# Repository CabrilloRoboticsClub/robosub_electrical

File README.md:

### Electrical stack up for RoboSub 2025 Lasershark

For documention take a look at:
https://github.com/CabrilloRoboticsClub/robosub_electrical/wiki

Desing requirments document:
https://docs.google.com/document/d/1Yq5ZJsRXAqFWiCNv81dD8MaTSv5xLRyw4zoX7664jJk/edit?usp=sharing

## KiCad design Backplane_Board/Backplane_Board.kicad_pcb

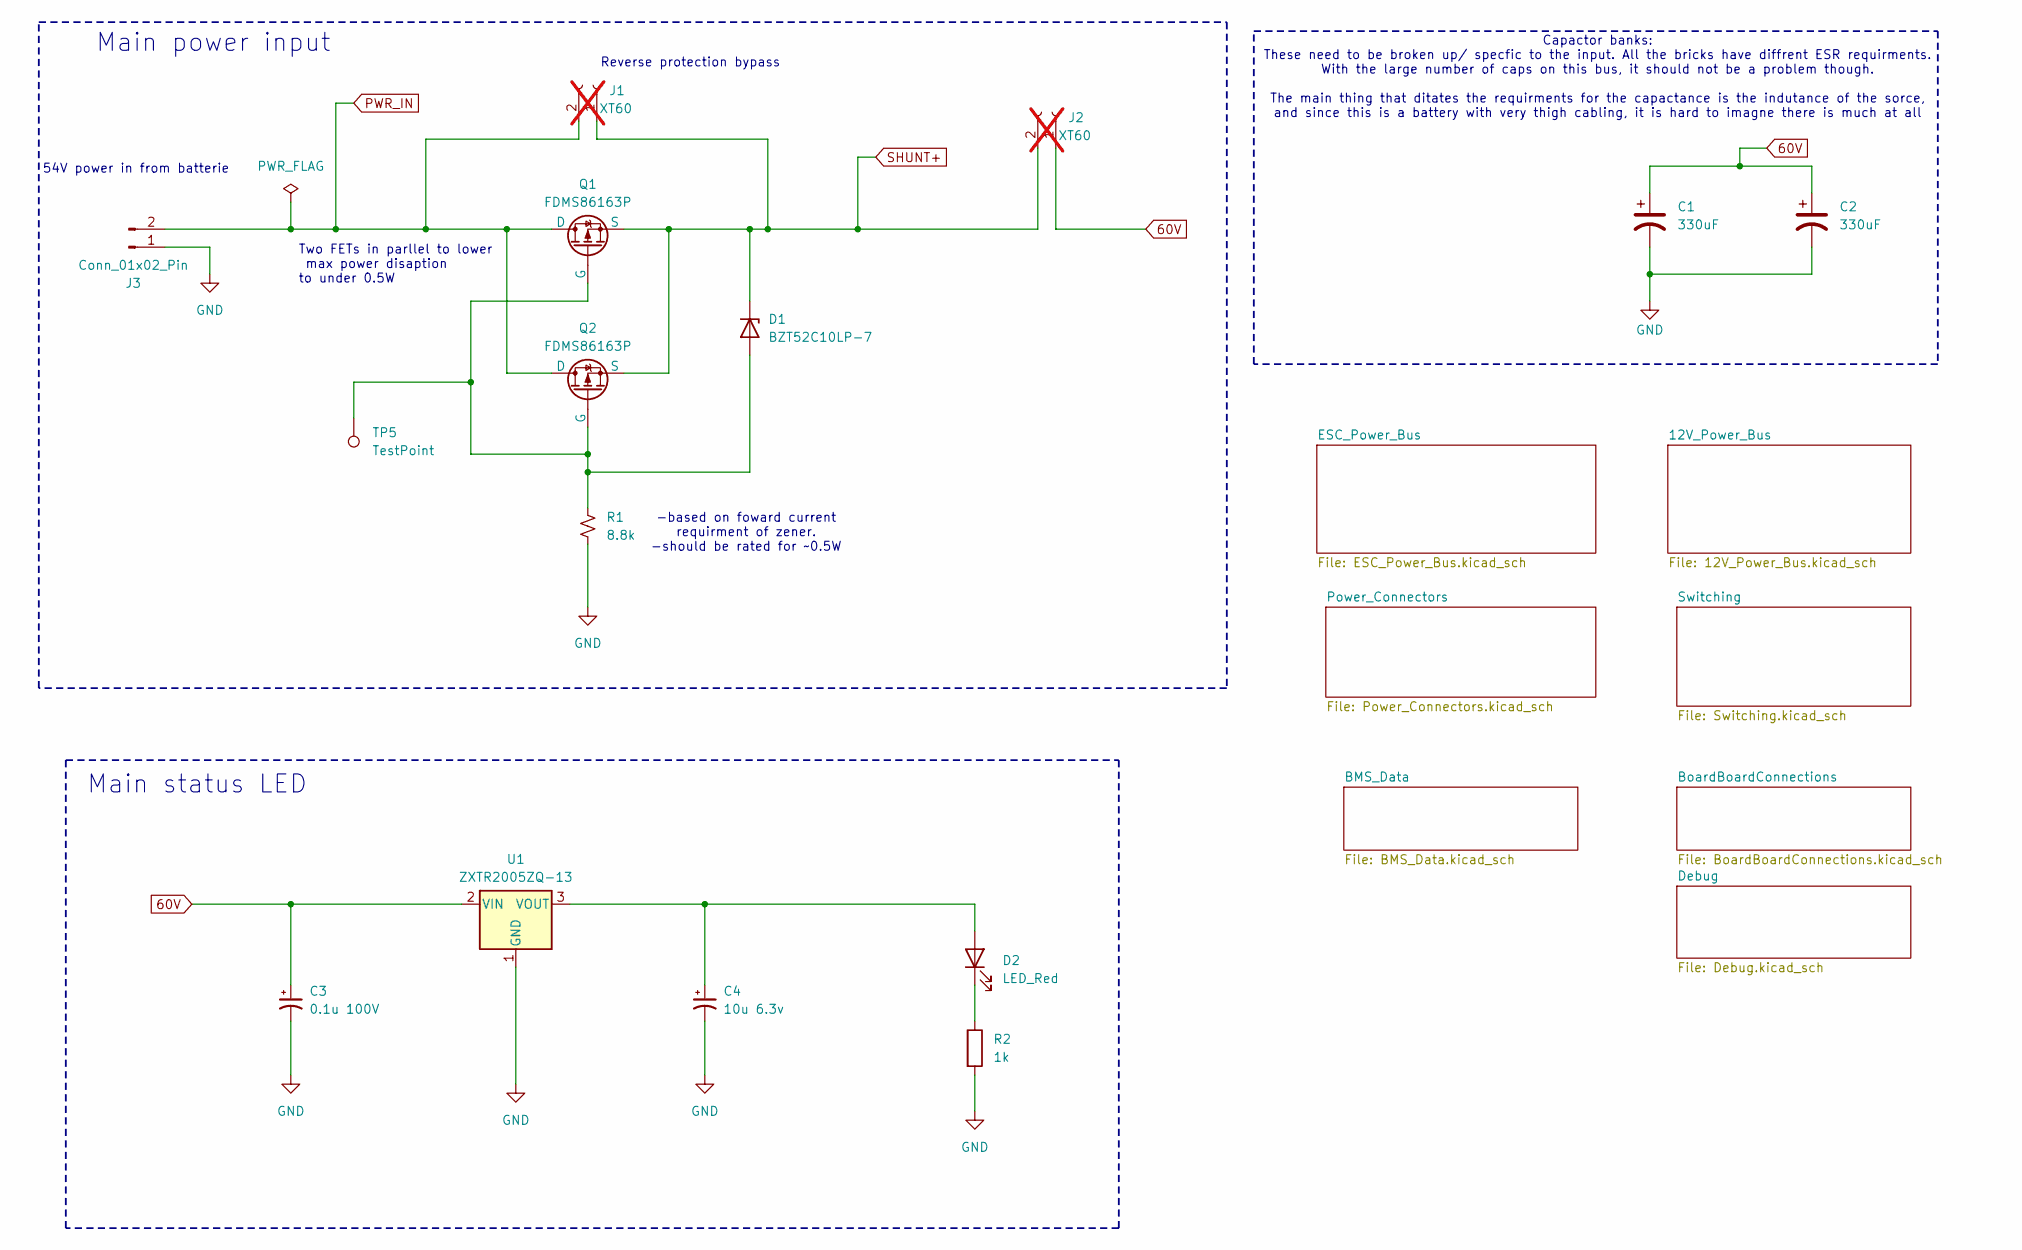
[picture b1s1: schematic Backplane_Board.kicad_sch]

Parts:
C1, C2: 330uF; CAP_EEVTG2A331M
C3: 0.1u 100V; C_1206_3216Metric_Pad1.33x1.80mm_HandSolder
C4: 10u 6.3v; C_1206_3216Metric_Pad1.33x1.80mm_HandSolder
D1: BZT52C10LP-7; D_SOD-882
D2: LED_Red; LED_0603_1608Metric
J1, J2: XT60; SolderWire-0.127sqmm_1x02_P3.7mm_D0.48mm_OD1mm; not fitted
J3: Conn_01x02_Pin; AMASS_XT60-M_1x02_P7.20mm_Vertical
Q1, Q2: FDMS86163P
R1: 8.8k; R_1206_3216Metric_Pad1.30x1.75mm_HandSolder
R2: 1k; R_0805_2012Metric_Pad1.20x1.40mm_HandSolder
TP5: TestPoint; TestPoint_Pad_2.5x2.5mm
U1: ZXTR2005ZQ-13; SOT-89-3_Handsoldering

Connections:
60V: C1.1, C2.1, C3.1, J2.1, U1.2 (VIN); also elsewhere on the board
GND: C1.2, C2.2, C3.2, C4.2, J3.1, R1.2, R2.2, U1.1 (GND); also elsewhere on the board
unnamed: D1.2 (A), Q1.2 (G), Q2.2 (G), R1.1, TP5.1
unnamed: C4.1, D2.2 (A), U1.3 (VOUT)
unnamed: D2.1 (K), R2.1
PWR_IN: J1.2, J3.2, Q1.1 (D), Q2.1 (D)
SHUNT+: D1.1 (K), J1.1, J2.2, Q1.3 (S), Q2.3 (S); also elsewhere on the board

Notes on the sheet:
Capactor banks: These need to be broken up/ specfic to the input. All the bricks have diffrent ESR requirments. With the large number of caps on this bus, it should not be a problem though. The main thing that ditates the requirments for the capactance is the indutance of the sorce, and since this 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
Main status LED
54V power in from batterie
Main power input
Reverse protection bypass
Two FETs in parllel to lower max power disaption to under 0.5W
-based on foward current requirment of zener. -should be rated for ~0.5W

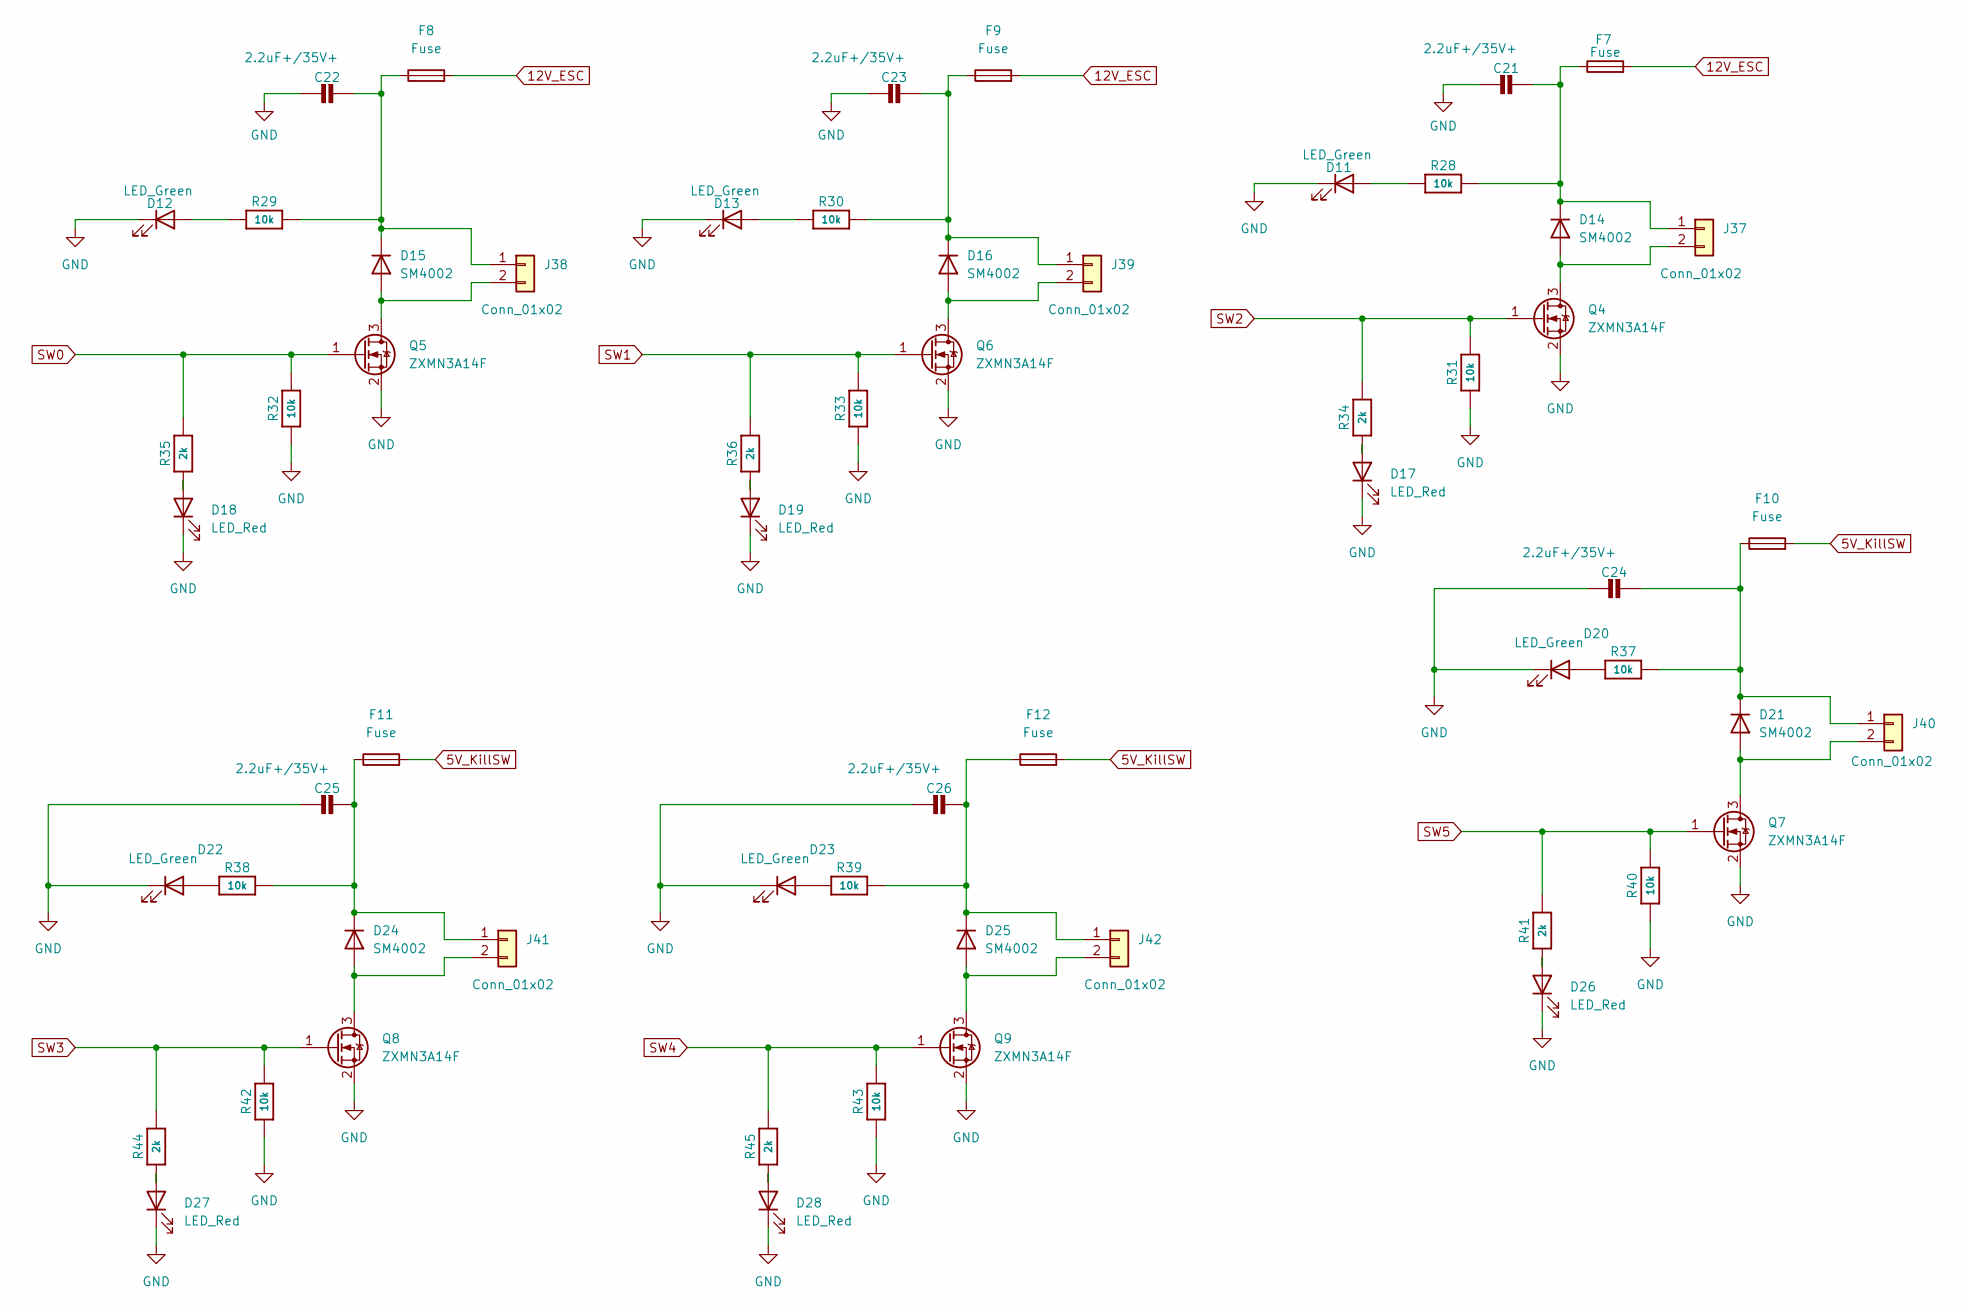
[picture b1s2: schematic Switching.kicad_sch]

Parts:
C21, C22, C23, C24, C25, C26: 2.2uF+/35V+; C_0805_2012Metric
D11, D12, D13, D20, D22, D23: LED_Green; LED_0603_1608Metric
D14, D15, D16, D21, D24, D25: SM4002; D_SOD-123F
D17, D18, D19, D26, D27, D28: LED_Red; LED_0603_1608Metric
F7, F8, F9, F10, F11, F12: Fuse; Fuse_0805_2012Metric
J37, J38, J39, J40, J41, J42: Conn_01x02; Molex_Micro-Latch_53253-0270_1x02_P2.00mm_Vertical
Q4, Q5, Q6, Q7, Q8, Q9: ZXMN3A14F; SOT-23
R28, R29, R30, R31, R32, R33, R37, R38, R39, R40, R42, R43: 10k; R_0805_2012Metric
R34, R35, R36, R41, R44, R45: 2k; R_0805_2012Metric

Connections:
5V_KillSW: F10.2, F11.2, F12.2; also elsewhere on the board
12V_ESC: F7.2, F8.2, F9.2; also elsewhere on the board
GND: C21.2, C22.2, C23.2, C24.2, C25.2, C26.2, D11.1 (K), D12.1 (K), D13.1 (K), D17.1 (K), D18.1 (K), D19.1 (K), D20.1 (K), D22.1 (K), D23.1 (K), D26.1 (K), D27.1 (K), D28.1 (K), Q4.2 (S), Q5.2 (S), Q6.2 (S), Q7.2 (S), Q8.2 (S), Q9.2 (S), R31.1, R32.1, R33.1, R40.1, R42.1, R43.1; also elsewhere on the board
unnamed: D11.2 (A), R28.1
unnamed: D12.2 (A), R29.1
unnamed: D13.2 (A), R30.1
unnamed: D14.2 (A), J37.2, Q4.3 (D)
unnamed: C21.1, D14.1 (K), F7.1, J37.1, R28.2
unnamed: D15.2 (A), J38.2, Q5.3 (D)
unnamed: C22.1, D15.1 (K), F8.1, J38.1, R29.2
unnamed: D16.2 (A), J39.2, Q6.3 (D)
unnamed: C23.1, D16.1 (K), F9.1, J39.1, R30.2
unnamed: D17.2 (A), R34.1
unnamed: D18.2 (A), R35.1
unnamed: D19.2 (A), R36.1
unnamed: D20.2 (A), R37.1
unnamed: D21.2 (A), J40.2, Q7.3 (D)
unnamed: C24.1, D21.1 (K), F10.1, J40.1, R37.2
unnamed: D22.2 (A), R38.1
unnamed: D23.2 (A), R39.1
unnamed: D24.2 (A), J41.2, Q8.3 (D)
unnamed: C25.1, D24.1 (K), F11.1, J41.1, R38.2
unnamed: D25.2 (A), J42.2, Q9.3 (D)
unnamed: C26.1, D25.1 (K), F12.1, J42.1, R39.2
unnamed: D26.2 (A), R41.1
unnamed: D27.2 (A), R44.1
unnamed: D28.2 (A), R45.1
SW0: Q5.1 (G), R32.2, R35.2; also elsewhere on the board
SW1: Q6.1 (G), R33.2, R36.2; also elsewhere on the board
SW2: Q4.1 (G), R31.2, R34.2; also elsewhere on the board
SW3: Q8.1 (G), R42.2, R44.2; also elsewhere on the board
SW4: Q9.1 (G), R43.2, R45.2; also elsewhere on the board
SW5: Q7.1 (G), R40.2, R41.2; also elsewhere on the board

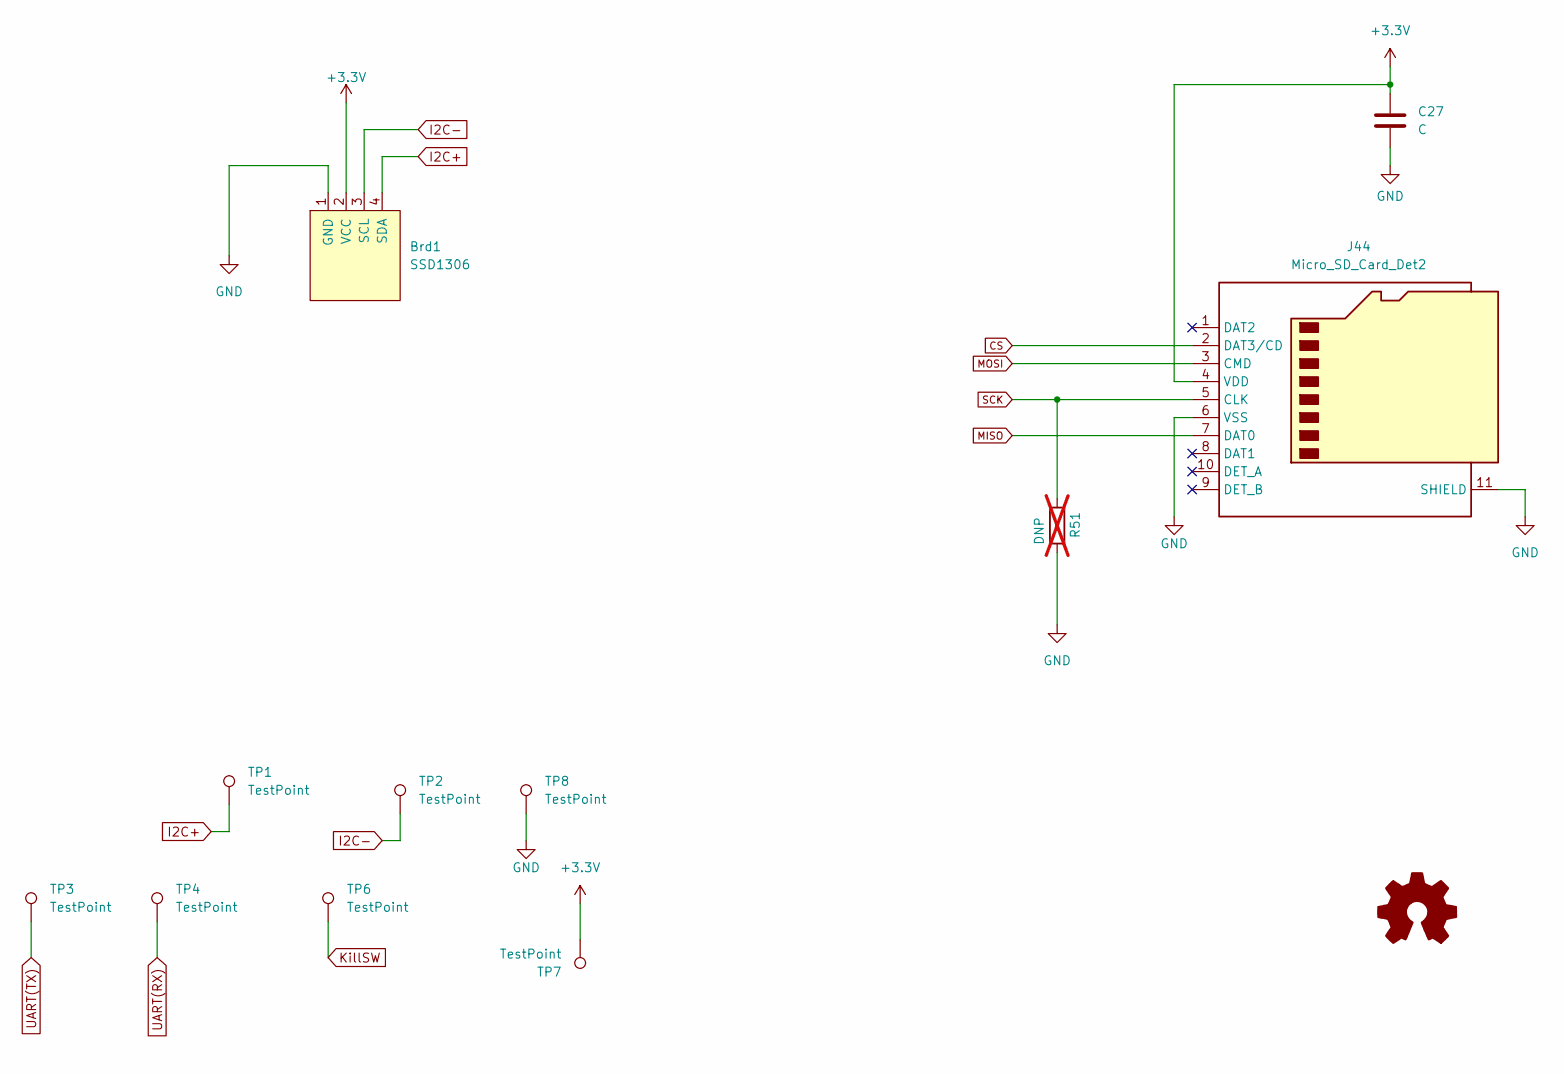
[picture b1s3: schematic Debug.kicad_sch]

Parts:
Brd1: SSD1306; MODULE_DM-OLED096-636
C27: C; C_1206_3216Metric_Pad1.33x1.80mm_HandSolder
J44: Micro_SD_Card_Det2; microSD_HC_Hirose_DM3D-SF
R51: DNP; R_0805_2012Metric_Pad1.20x1.40mm_HandSolder; not fitted
TP1, TP2, TP8: TestPoint; TestPoint_Loop_D1.80mm_Drill1.0mm_Beaded
TP3, TP4, TP6, TP7: TestPoint; TestPoint_Pad_2.5x2.5mm

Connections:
+3.3V: Brd1.2 (VCC), C27.1, J44.4 (VDD), TP7.1; also elsewhere on the board
CS: J44.2 (DAT3/CD); also elsewhere on the board
GND: Brd1.1 (GND), C27.2, J44.6 (VSS), J44.11 (SHIELD), R51.1, TP8.1; also elsewhere on the board
I2C+: Brd1.4 (SDA), TP1.1; also elsewhere on the board
I2C-: Brd1.3 (SCL), TP2.1; also elsewhere on the board
KillSW: TP6.1; also elsewhere on the board
MISO: J44.7 (DAT0); also elsewhere on the board
MOSI: J44.3 (CMD); also elsewhere on the board
SCK: J44.5 (CLK), R51.2; also elsewhere on the board
UART(RX): TP4.1; also elsewhere on the board
UART(TX): TP3.1; also elsewhere on the board

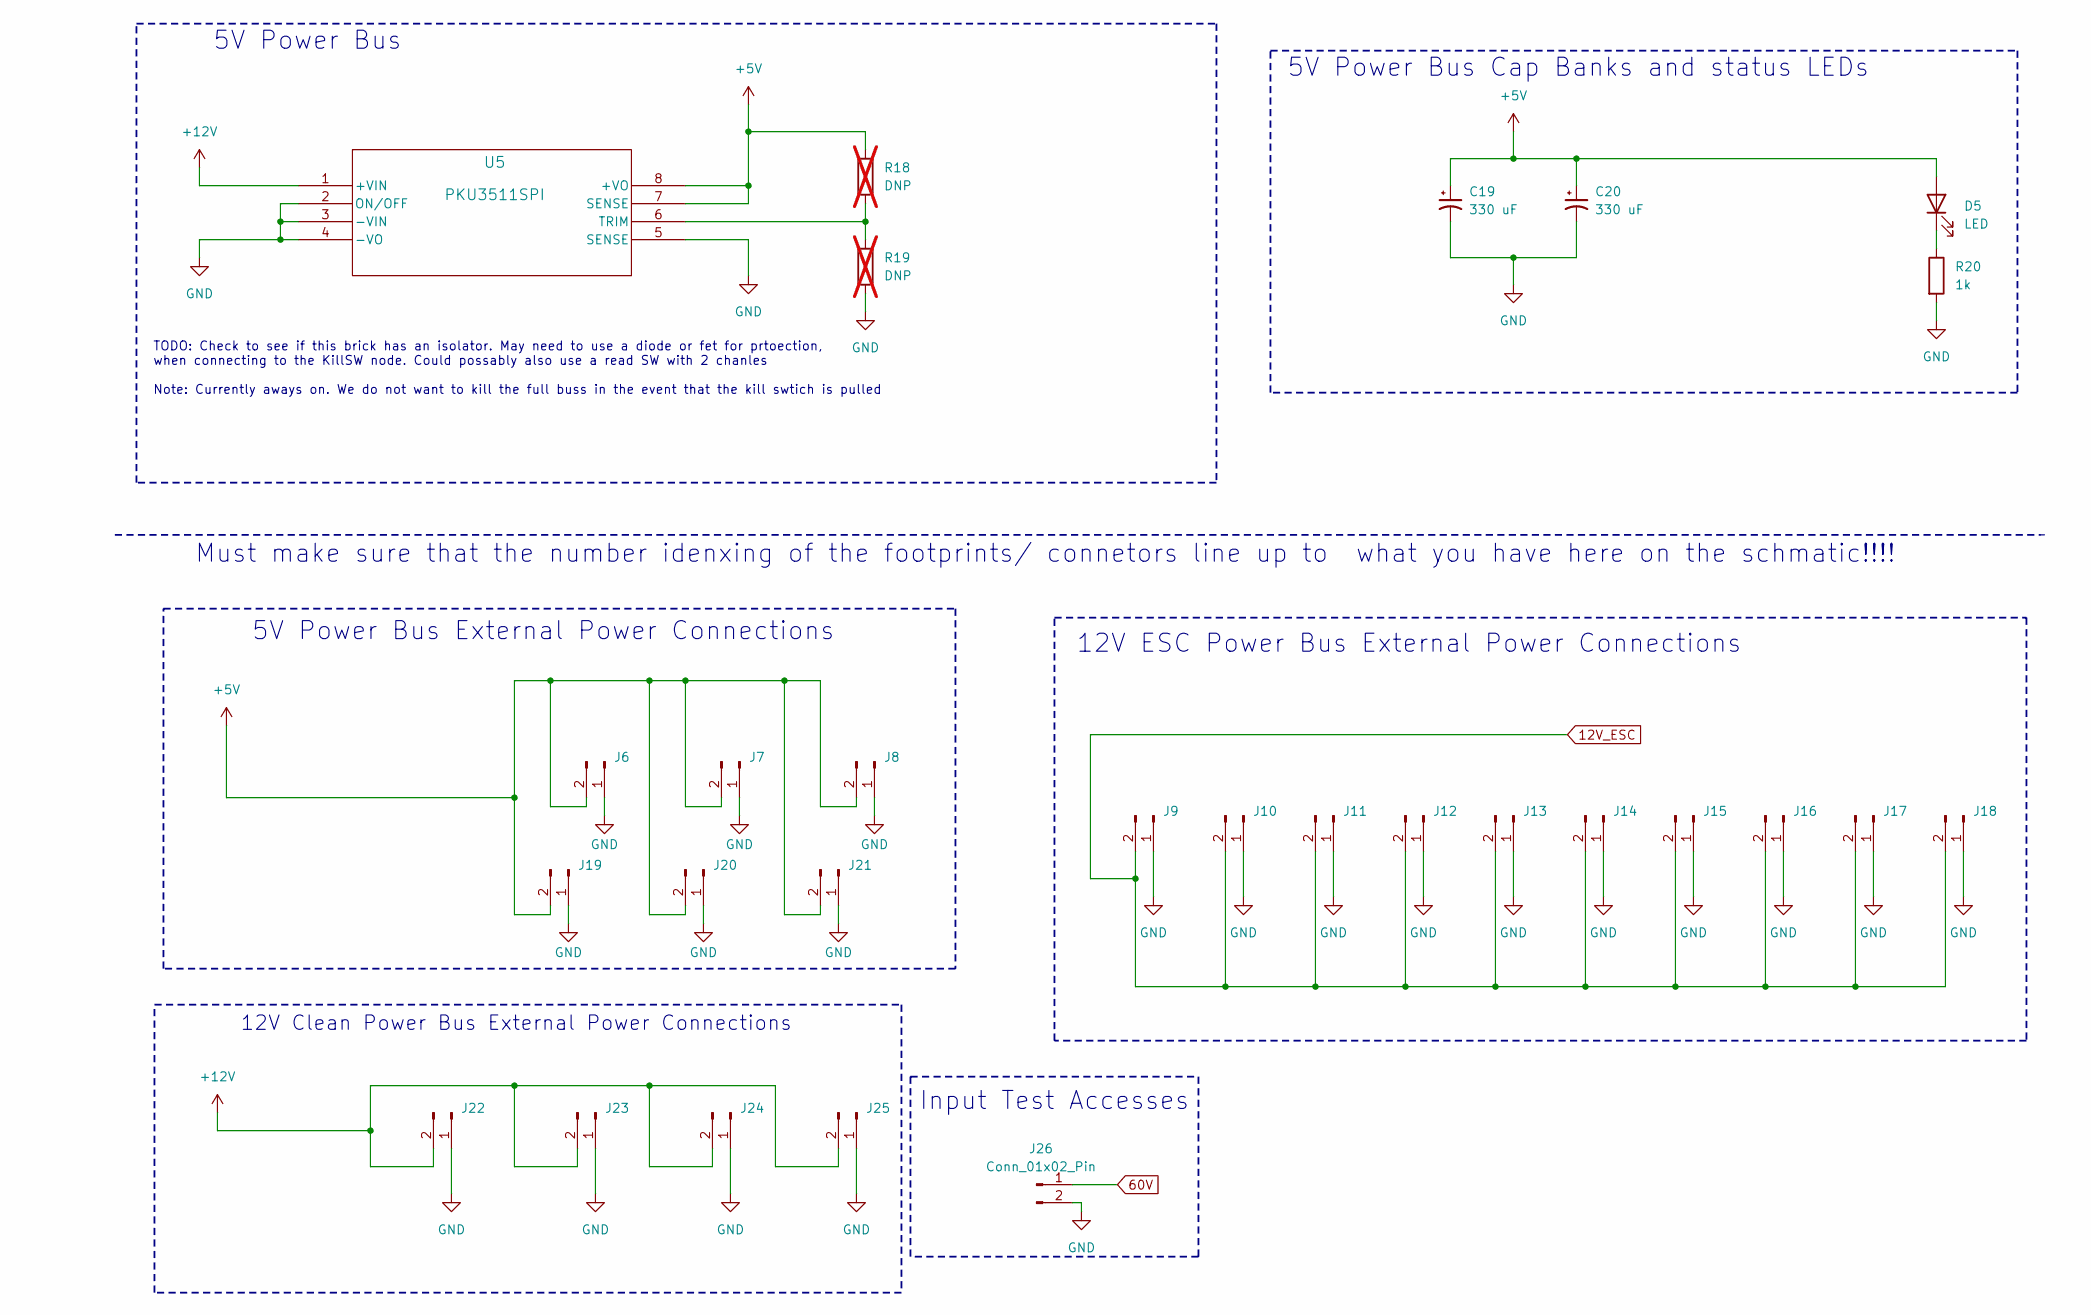
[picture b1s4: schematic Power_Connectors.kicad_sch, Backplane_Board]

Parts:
C19, C20: 330 uF; CP_Elec_6.3x7.7
D5: LED; LED_0603_1608Metric
J6, J7, J8, J19, J20, J21: Conn_01x02_Pin; TerminalBlock_4Ucon_1x02_P3.50mm_Horizontal_updated
J9, J10, J11, J12, J13, J14, J15, J16, J17, J18, J22, J23, J24, J25: Conn_01x02_Pin; AMASS_XT30U-M_1x02_P5.0mm_Vertical_IW_3d
J26: Conn_01x02_Pin; TestPoint_2Pads_Pitch2.54mm_Drill0.8mm
R18, R19: DNP; L_1206_3216Metric; not fitted
R20: 1k; R_0805_2012Metric_Pad1.20x1.40mm_HandSolder
U5: PKU3511SPI; PKU 3500S_FPM

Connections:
12V_ESC: J9.2, J10.2, J11.2, J12.2, J13.2, J14.2, J15.2, J16.2, J17.2, J18.2; also elsewhere on the board
60V: J26.1; also elsewhere on the board
+5V: C19.1, C20.1, D5.2 (A), J6.2, J7.2, J8.2, J19.2, J20.2, J21.2, R18.1, U5.7 (SENSE), U5.8 (+VO); also elsewhere on the board
+12V: J22.2, J23.2, J24.2, J25.2, U5.1 (+VIN); also elsewhere on the board
GND: C19.2, C20.2, J6.1, J7.1, J8.1, J9.1, J10.1, J11.1, J12.1, J13.1, J14.1, J15.1, J16.1, J17.1, J18.1, J19.1, J20.1, J21.1, J22.1, J23.1, J24.1, J25.1, J26.2, R19.2, R20.2, U5.2 (ON/OFF), U5.3 (-VIN), U5.4 (-VO), U5.5 (SENSE); also elsewhere on the board
unnamed: D5.1 (K), R20.1
unnamed: R18.2, R19.1, U5.6 (TRIM)

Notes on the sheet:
12V Clean Power Bus External Power Connections
Must make sure that the number idenxing of the footprints/ connetors line up to what you have here on the schmatic!!!!
5V Power Bus
5V Power Bus Cap Banks and status LEDs
5V Power Bus External Power Connections
12V ESC Power Bus External Power Connections
TODO: Check to see if this brick has an isolator. May need to use a diode or fet for prtoection, when connecting to the KillSW node. Could possably also use a read SW with 2 chanles Note: Currently aways on. We do not want to kill the full buss in the event that the kill swtich is pulled
Input Test Accesses

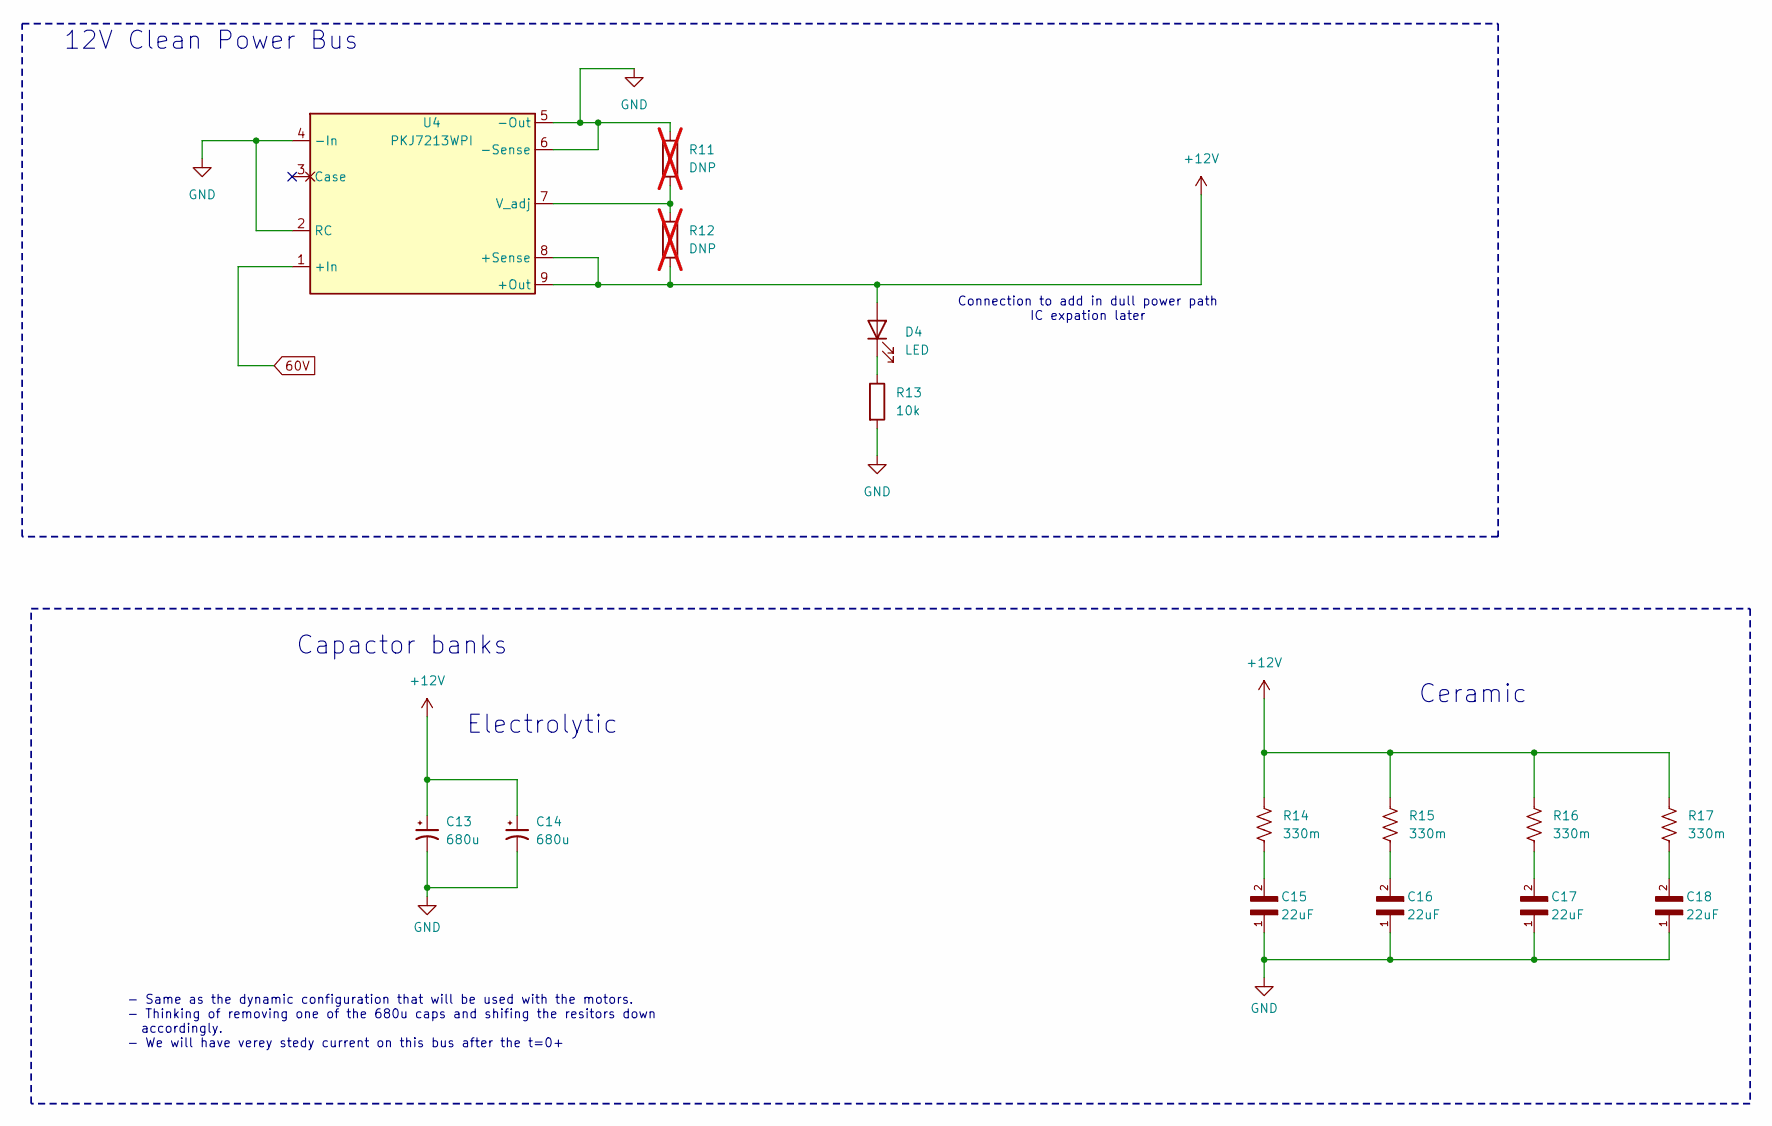
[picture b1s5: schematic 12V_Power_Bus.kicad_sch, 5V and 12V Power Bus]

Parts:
C13, C14: 680u; CP_Radial_D13.0mm_P5.00mm
C15, C16, C17, C18: 22uF; C_1206_3216Metric_Pad1.33x1.80mm_HandSolder
D4: LED; LED_0603_1608Metric
R11, R12: DNP; L_1206_3216Metric; not fitted
R13: 10k; R_0805_2012Metric_Pad1.20x1.40mm_HandSolder
R14, R15, R16, R17: 330m; RES_KDV12_OHM-L
U4: PKJ7213WPI

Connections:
60V: U4.1 (+In); also elsewhere on the board
+12V: C13.1, C14.1, D4.2 (A), R12.2, R14.1, R15.1, R16.1, R17.1, U4.8 (+Sense), U4.9 (+Out); also elsewhere on the board
GND: C13.2, C14.2, C15.1, C16.1, C17.1, C18.1, R11.1, R13.2, U4.2 (RC), U4.4 (-In), U4.5 (-Out), U4.6 (-Sense); also elsewhere on the board
unnamed: C15.2, R14.2
unnamed: C16.2, R15.2
unnamed: C17.2, R16.2
unnamed: C18.2, R17.2
unnamed: D4.1 (K), R13.1
unnamed: R11.2, R12.1, U4.7 (V_adj)

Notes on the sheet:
Ceramic
Electrolytic
Connection to add in dull power path IC expation later
12V Clean Power Bus
- Same as the dynamic configuration that will be used with the motors. - Thinking of removing one of the 680u caps and shifing the resitors down accordingly. - We will have verey stedy current on this bus after the t=0+
Capactor banks

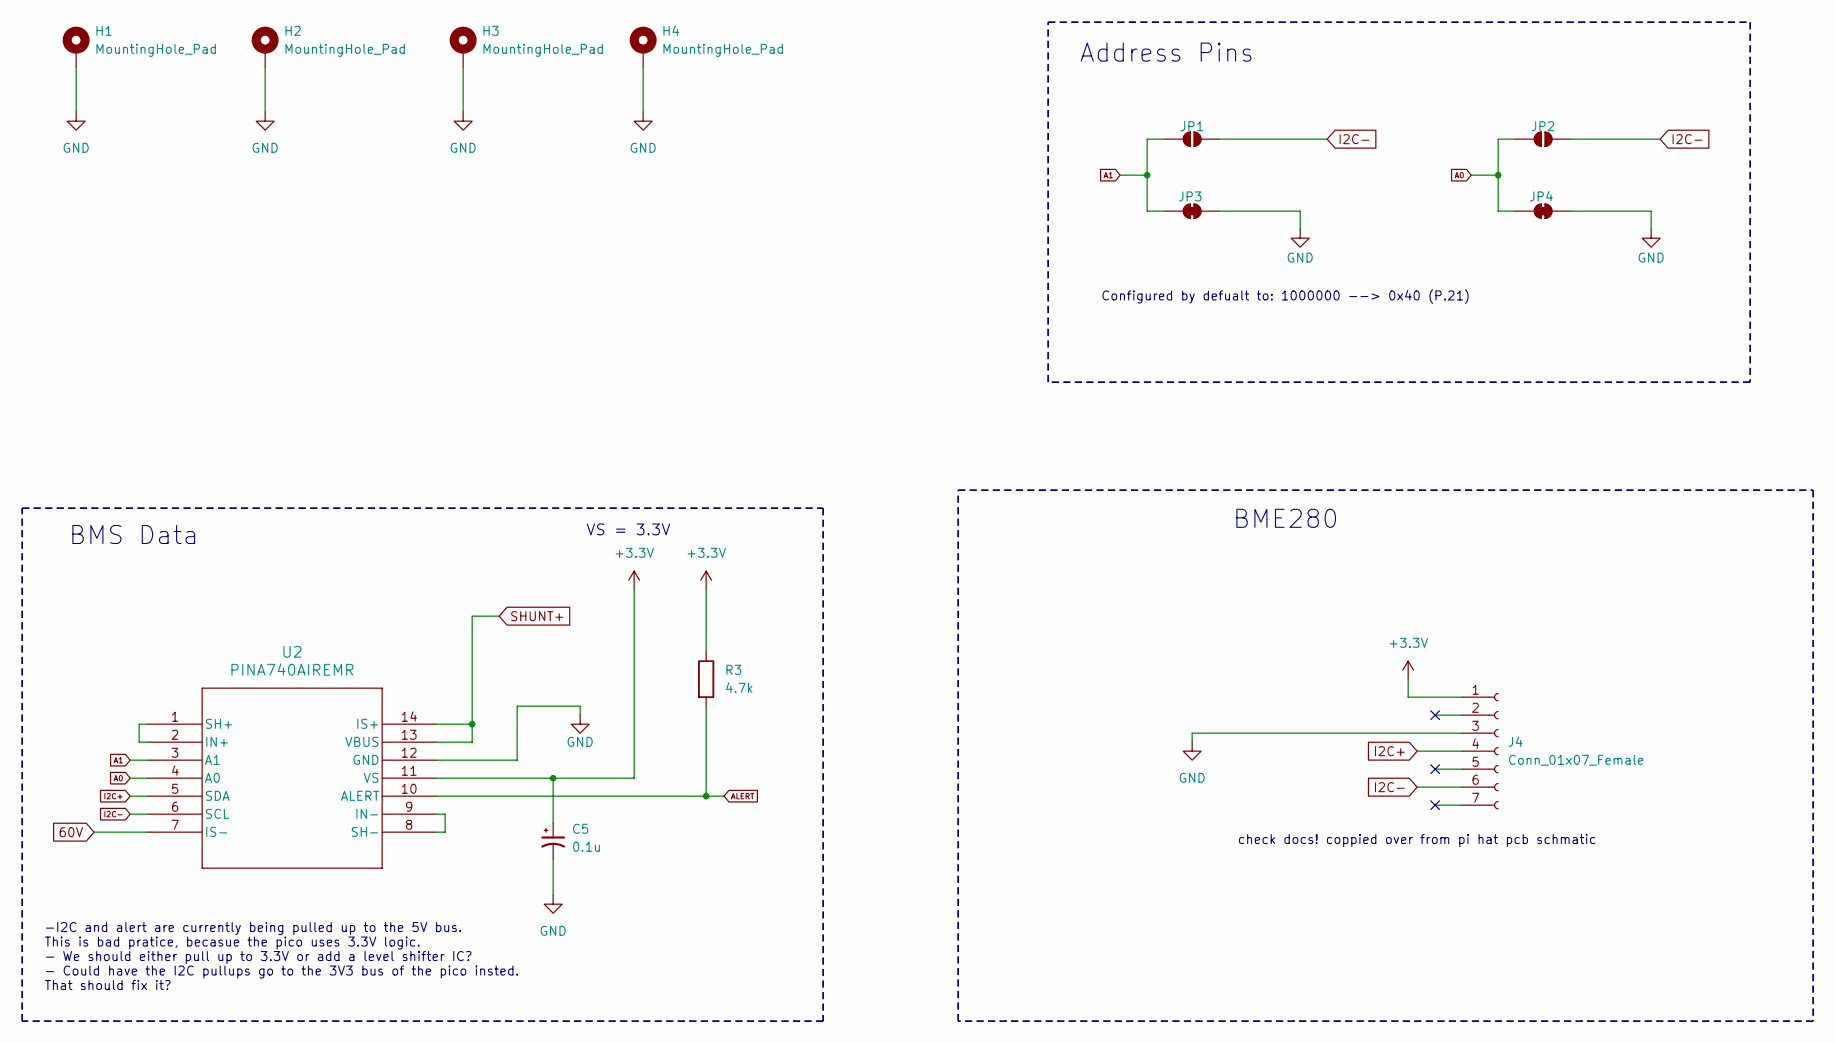
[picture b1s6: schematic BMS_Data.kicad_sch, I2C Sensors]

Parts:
C5: 0.1u; C_0603_1608Metric_Pad1.08x0.95mm_HandSolder
H1, H2, H3, H4: MountingHole_Pad; MountingHole_4.3mm_M4_Pad_Via
J4: Conn_01x07_Female; PinSocket_1x07_P2.54mm_Vertical
JP1, JP2: SolderJumper_2_Open; SolderJumper-2_P1.3mm_Open_RoundedPad1.0x1.5mm
JP3, JP4: SolderJumper_2_Bridged; SolderJumper-2_P1.3mm_Bridged_RoundedPad1.0x1.5mm
R3: 4.7k; R_0805_2012Metric_Pad1.20x1.40mm_HandSolder
U2: PINA740AIREMR; INA740BIREMR

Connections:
60V: U2.7 (IS-); also elsewhere on the board
+3.3V: C5.1, J4.1, R3.1, U2.11 (VS); also elsewhere on the board
A0: JP2.1 (A), JP4.1 (A), U2.4 (A0)
A1: JP1.1 (A), JP3.1 (A), U2.3 (A1)
ALERT: R3.2, U2.10 (ALERT); also elsewhere on the board
GND: C5.2, H1.1, H2.1, H3.1, H4.1, J4.3, JP3.2 (B), JP4.2 (B), U2.12 (GND); also elsewhere on the board
I2C+: J4.4, U2.5 (SDA); also elsewhere on the board
I2C-: J4.6, JP1.2 (B), JP2.2 (B), U2.6 (SCL); also elsewhere on the board
unnamed: U2.1 (SH+), U2.2 (IN+)
unnamed: U2.8 (SH-), U2.9 (IN-)
SHUNT+: U2.13 (VBUS), U2.14 (IS+); also elsewhere on the board

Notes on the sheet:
BMS Data
BME280
check docs! coppied over from pi hat pcb schmatic
Address Pins
VS = 3.3V
-I2C and alert are currently being pulled up to the 5V bus. This is bad pratice, becasue the pico uses 3.3V logic. - We should either pull up to 3.3V or add a level shifter IC? - Could have the I2C pullups go to the 3V3 bus of the pico insted. That should fix it?
Configured by defualt to: 1000000 --> 0x40 (P.21)
